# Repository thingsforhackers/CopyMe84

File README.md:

# CopyMe84

## Introduction

This repo contains the source code and KiCad project files for our CopyMe84 game kit.

The CopyMe84 game plays very similar to the classic "Simon Says" electionic game.

A complete kit looks like this:

Please visit [our store](https://thingsforhackers.com/store/) to purchase this kit.

When 1st powered on, i.e. when you insert the battery, it will play a nice('ish) title tune. After one loop of this tune, the game will enter power saving mode, press any button to wake it up.

To start the game, press any button during the title tune. The game play consitst of remember the sequence of LEDs, and pressing the corrosponding buttons in the correct order to repeat the sequence. Each sucessful loop the game will add another step to the sequence. To help, each LED flash is accompanied by a different beeper tone.

## HW Build Instructions

Full HW build instructions can be found on our [blog](https://thingsforhackers.com/post/build-instructions-copyme-84a/).

## SW Build Instructions

The kit contains a pre-programmed Ateml ATtiny84A microcontroller. However, as this is an open souce product you are albe to, infact we strongly encourge you to, modify, build and try out the code for yourself.

Inorder to build the code, you'll need a compiler that can target the Ateml AVR range of products. I would suggest starting [here](http://www.nongnu.org/avr-libc/user-manual/index.html).

If you're lucky enough to be on some sort of Linux box, I've written up [full instructions](https://thingsforhackers.com/post/installing-avr-libc/) on how to install the gcc tool chain for the AVRs.

Assuming you've got the gcc toolchain installed, the following shows you how to build the code:

If you haven't already, clone the github repo: `git clone git@github.com:thingsforhackers/CopyMe84.git`

Then simply `cd CopyMe84`, and type `make`.

If all went well, inside of the *obj* directory, you will find *copyme84.bin* & *copyme84.hex*, you should be able to use one of these files to program the ATtiny84A.

We use the *Mini Pro TL866CS programmer* to program pretty much all our products. You can pick one up from our [eBay store](http://www.ebay.co.uk/usr/thingsforhackers).

Which ever method you use to program, please ensure the *fuse* bits of the ATtiny84A are programmed as follows:

Byte | Value
-----|------
Low | 0x62
High | 0x5F
Ext | 0xFF

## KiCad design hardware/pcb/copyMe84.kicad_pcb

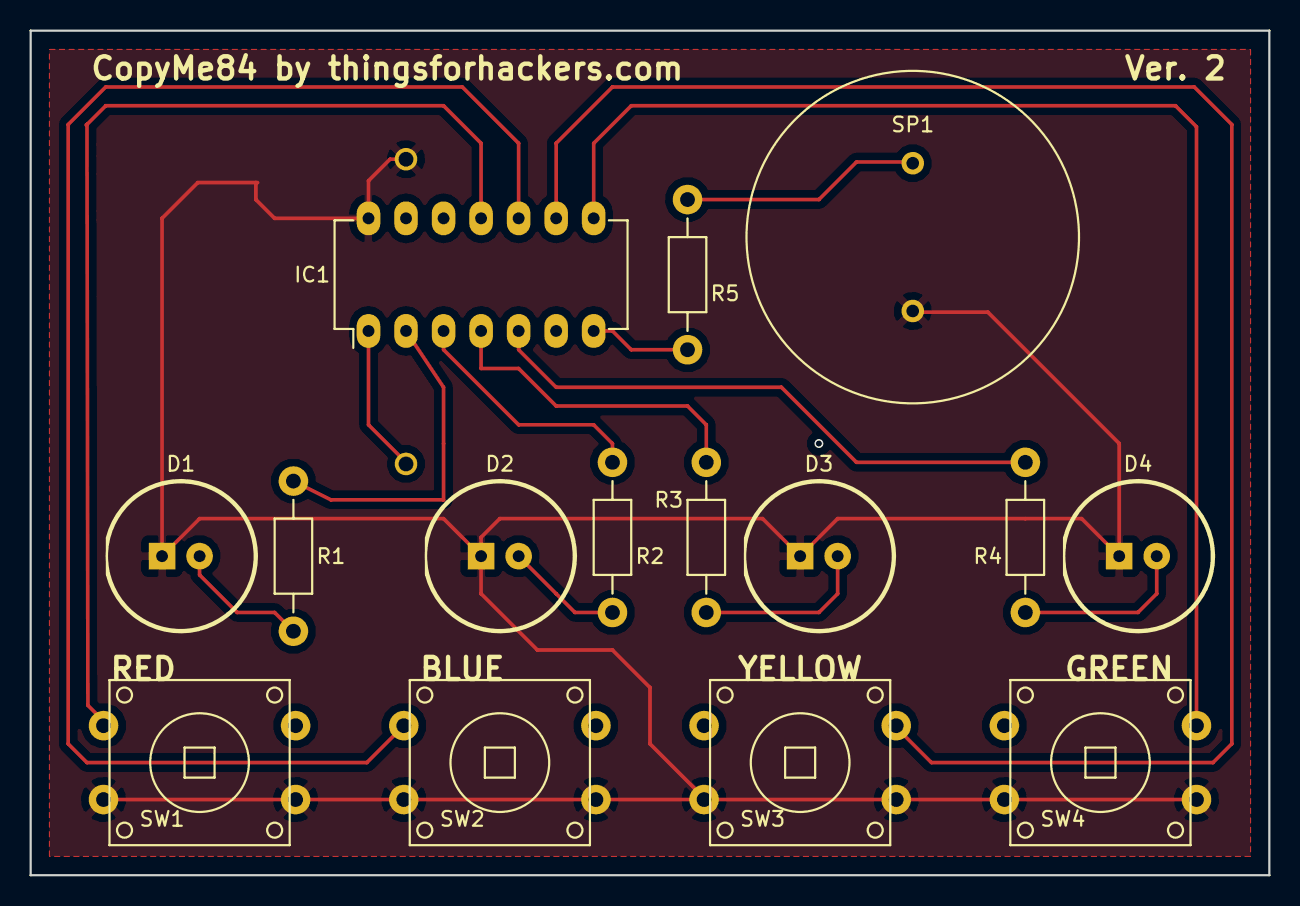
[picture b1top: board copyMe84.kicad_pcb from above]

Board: 2 copper layers, 83.8 x 57.1 mm, 16 parts (1 on the bottom side), 16 nets.

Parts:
BT1: CR2477
D1: RED; LED-10MM
D2: BLUE; LED-10MM
D3: YELLOW; LED-10MM
D4: GREEN; LED-10MM
IC1: ATTINY84A-P; DIP-14_W7.62mm_LongPads
R1, R2, R3, R4, R5: 220; Resistor_Horizontal_RM10mm
SP1: SPEAKER; Speaker - MCABS-201-RC
SW1, SW2, SW3, SW4: KFC-012-7.3

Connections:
/SPEAKER: IC1.7, R5.1
/ledBLUE: IC1.3, R2.1
/ledGREEN: IC1.5, R4.1
/ledRED: IC1.2, R1.1
/ledYELLOW: IC1.4, R3.1
/swBLUE: IC1.10, SW2.1
/swGREEN: IC1.8, SW4.4
/swRED: IC1.11, SW1.1
/swYELLOW: IC1.9, SW3.4
Earth: BT1.2, D1.1, D2.1, D3.1, D4.1, IC1.14, SP1.2, SW1.2, SW1.3, SW2.2, SW2.3, SW3.2, SW3.3, SW4.2, SW4.3
unnamed: BT1.1, IC1.1
unnamed: D1.2, R1.2
unnamed: D2.2, R2.2
unnamed: D3.2, R3.2
unnamed: D4.2, R4.2
unnamed: R5.2, SP1.1

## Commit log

2016-05-04 git ignore
2016-06-11 Initial working version.
2016-06-12 Working ish
2016-06-12 Workinggit diff!
2016-06-12 Added missing files
2016-06-15 Improve randomness of sequences.
2016-06-15 Added title tune
2016-06-25 Removed old hw
2016-06-25 Updated with latest HW
2016-11-29 Docs & Stugg
2016-12-10 Added cscope stuff
2016-12-13 Added deep sleep at end of 1st music run.
2016-12-15 Added builds + tidyup
2016-12-19 Added store link
2017-01-17 Updated missing libs
2017-06-24 Fixed up code for Ver 2.1 board
2017-06-24 V2.1
2017-12-17 update kicad project
2018-01-15 Commit of v2.1 .hex file
